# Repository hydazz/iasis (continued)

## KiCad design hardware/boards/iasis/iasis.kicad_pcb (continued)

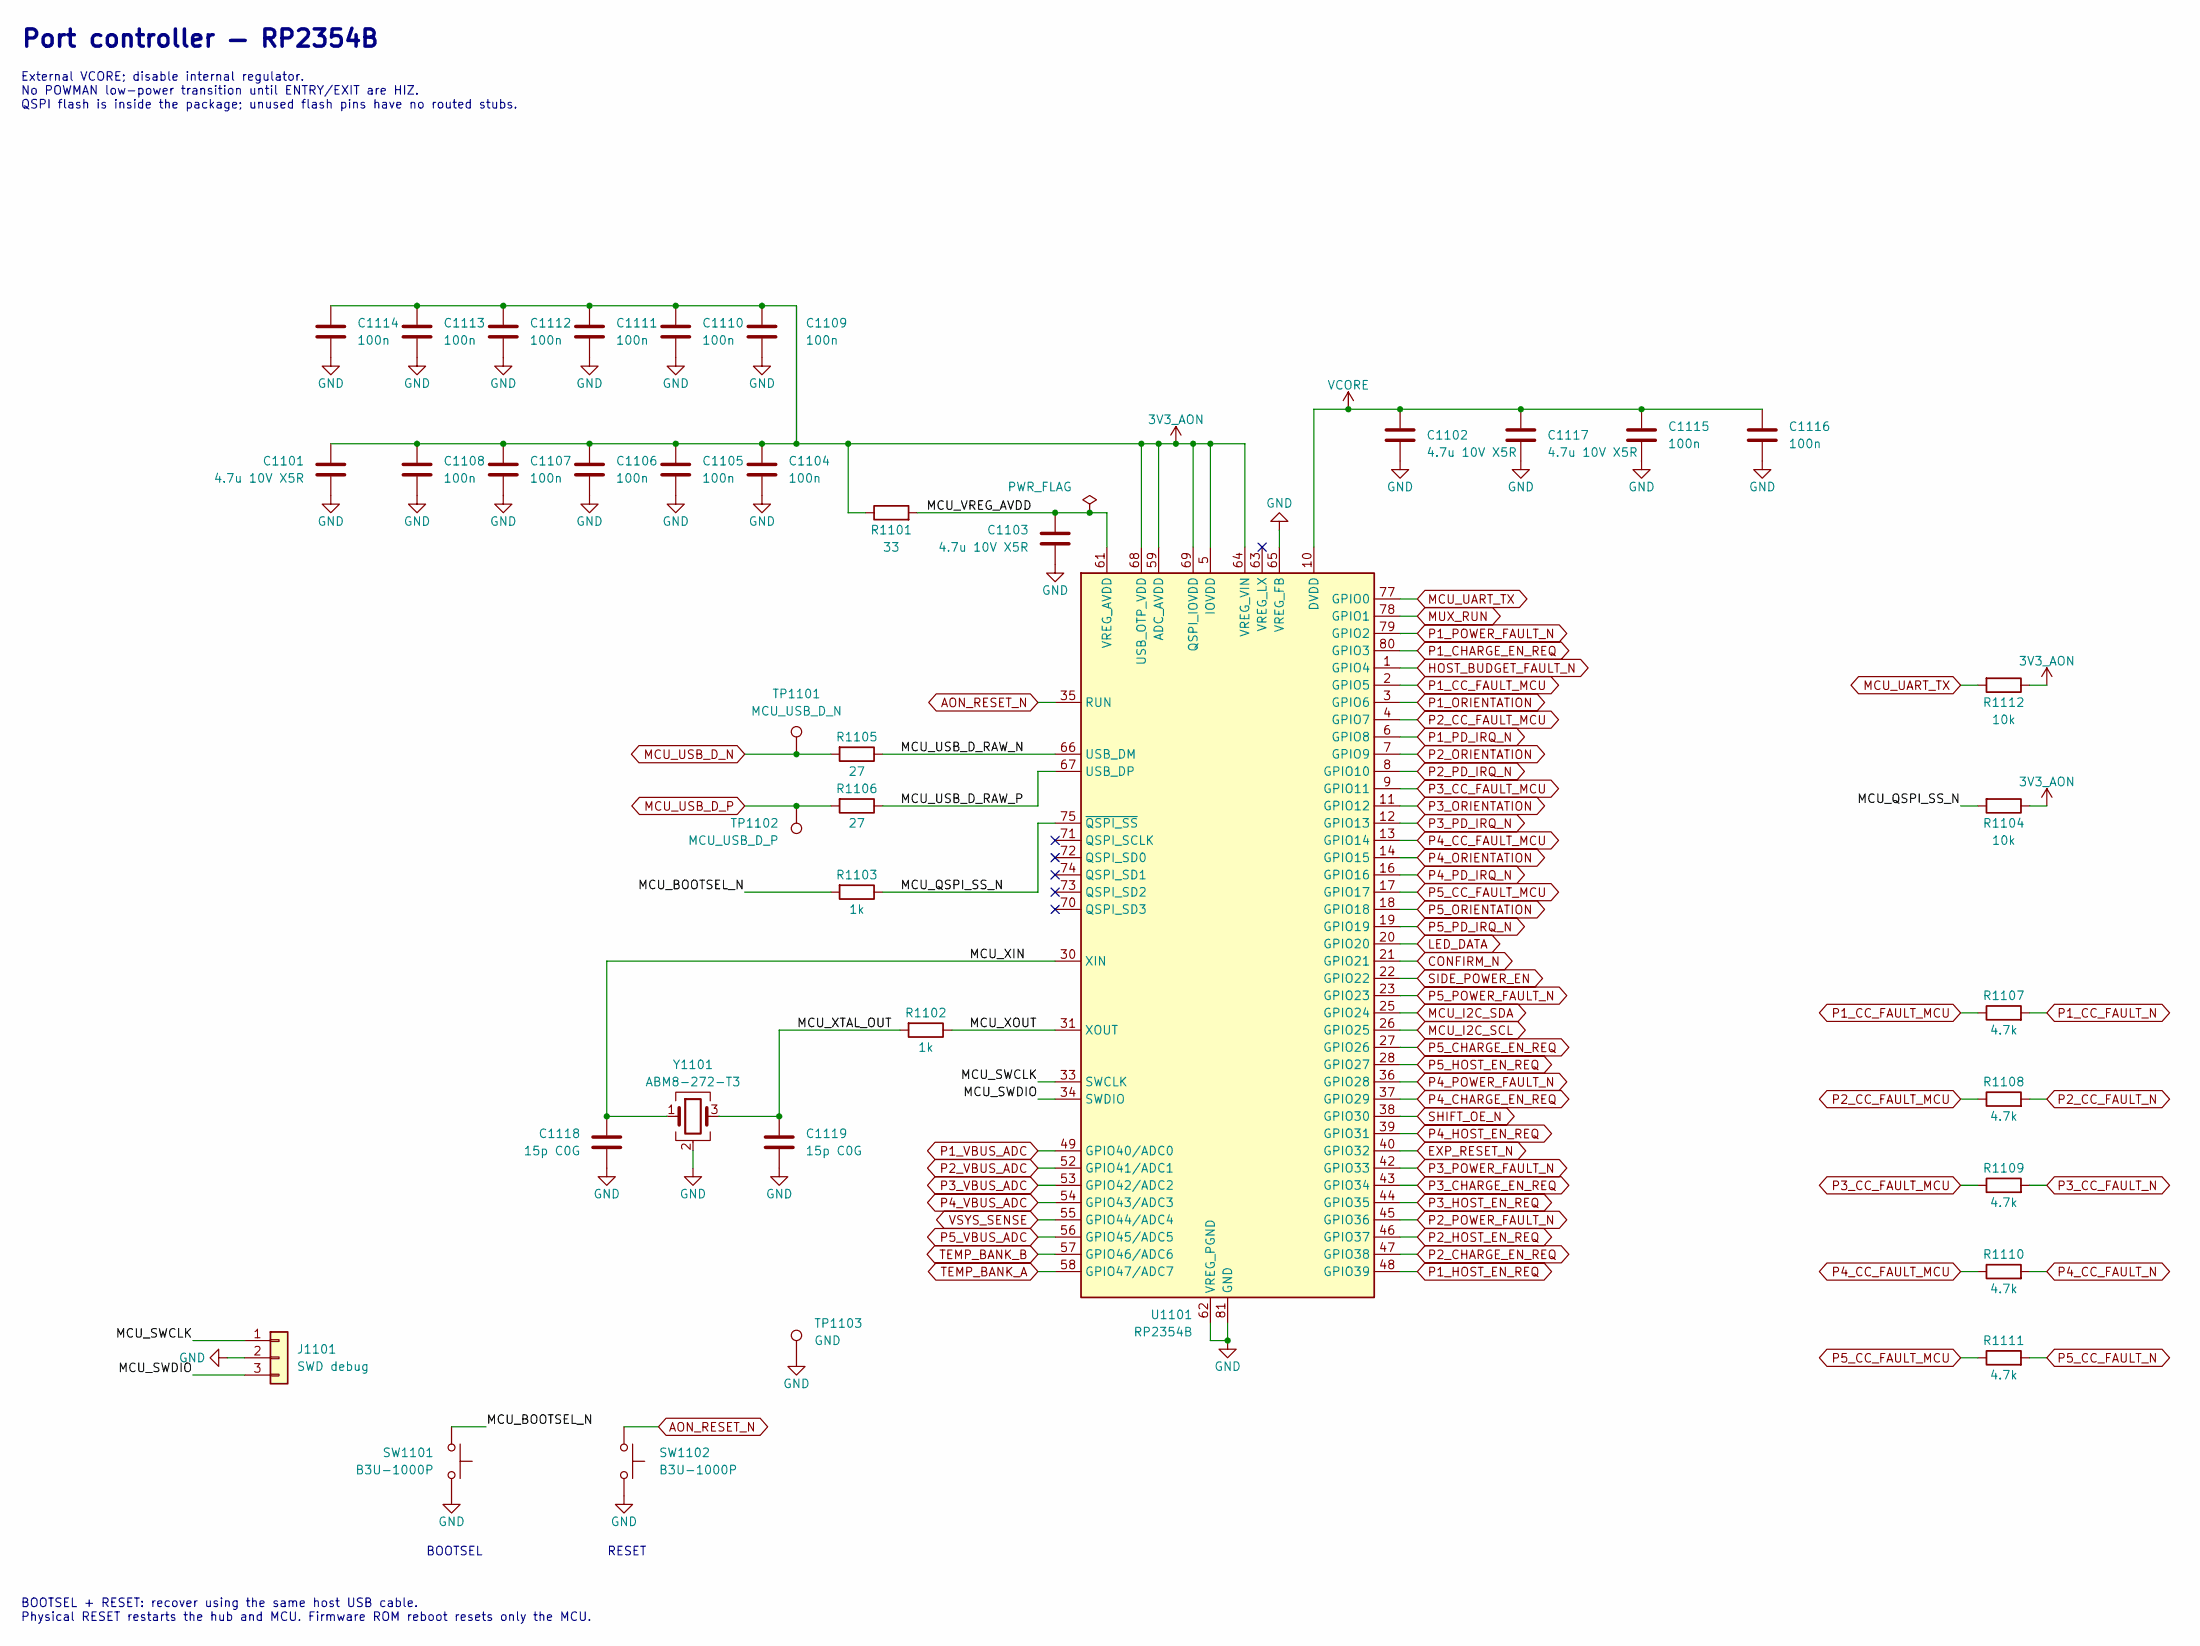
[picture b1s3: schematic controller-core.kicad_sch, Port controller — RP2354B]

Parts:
C1101, C1102: 4.7u 10V X5R; C_0402_1005Metric_WideGap; MPN CL05A475MP5NRNC; LCSC C23733
C1103, C1117: 4.7u 10V X5R; C_0402_1005Metric; MPN CL05A475MP5NRNC; LCSC C23733
C1104, C1105, C1106, C1107, C1108, C1109, C1110, C1111, C1112, C1113, C1114, C1115, C1116: 100n; C_0402_1005Metric; MPN CL05B104KO5NNNC; LCSC C1525
C1118, C1119: 15p C0G; C_0402_1005Metric; MPN 0402CG150J500NT; LCSC C1548
J1101: SWD debug; SolderPads_1x03_P2.54mm
R1101: 33; R_0402_1005Metric; MPN 0402WGF330JTCE; LCSC C25105
R1102, R1103: 1k; R_0402_1005Metric; MPN 0402WGF1001TCE; LCSC C11702
R1104, R1112: 10k; R_0402_1005Metric; MPN 0402WGF1002TCE; LCSC C25744
R1105, R1106: 27; R_0402_1005Metric; MPN RC-02K27R0FT; LCSC C140174
R1107, R1108, R1109, R1110, R1111: 4.7k; R_0402_1005Metric; MPN 0402WGF4701TCE; LCSC C25900
SW1101, SW1102: B3U-1000P; SW_SPST_B3U-1000P; MPN B3U-1000P; LCSC C231329
TP1101: MCU_USB_D_N; TestPoint_Pad_D0.5mm
TP1102: MCU_USB_D_P; TestPoint_Pad_D0.5mm
TP1103: GND; TestPoint_Pad_D1.0mm
U1101: RP2354B; QFN-80-1EP_10x10mm_P0.4mm_EP3.4x3.4mm; MPN RP2354B; LCSC C39843328
Y1101: ABM8-272-T3; Crystal_SMD_3225-4Pin_3.2x2.5mm; MPN ABM8-272-T3; LCSC C20625731

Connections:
3V3_AON: C1101.1, C1104.1, C1105.1, C1106.1, C1107.1, C1108.1, C1109.1, C1110.1, C1111.1, C1112.1, C1113.1, C1114.1, R1101.1, R1104.1, R1112.1, U1101.5 (IOVDD), U1101.15 (IOVDD), U1101.24 (IOVDD), U1101.29 (IOVDD), U1101.41 (IOVDD), U1101.50 (IOVDD), U1101.59 (ADC_AVDD), U1101.60 (IOVDD), U1101.64 (VREG_VIN), U1101.68 (USB_OTP_VDD), U1101.69 (QSPI_IOVDD), U1101.76 (IOVDD); also elsewhere on the board
/RP2354 controller/MCU_BOOTSEL_N: R1103.2, SW1101.1
/RP2354 controller/MCU_QSPI_SS_N: R1103.1, R1104.2, U1101.75 (~QSPI_SS)
/RP2354 controller/MCU_SWCLK: J1101.1, U1101.33 (SWCLK)
/RP2354 controller/MCU_SWDIO: J1101.3, U1101.34 (SWDIO)
/RP2354 controller/MCU_USB_D_RAW_N: R1105.1, U1101.66 (USB_DM)
/RP2354 controller/MCU_USB_D_RAW_P: R1106.1, U1101.67 (USB_DP)
/RP2354 controller/MCU_VREG_AVDD: C1103.1, R1101.2, U1101.61 (VREG_AVDD)
/RP2354 controller/MCU_XIN: C1118.1, U1101.30 (XIN), Y1101.1
/RP2354 controller/MCU_XOUT: R1102.1, U1101.31 (XOUT)
/RP2354 controller/MCU_XTAL_OUT: C1119.1, R1102.2, Y1101.3
AON_RESET_N: SW1102.1, U1101.35 (RUN); also elsewhere on the board
CONFIRM_N: U1101.21 (GPIO21); also elsewhere on the board
EXP_RESET_N: U1101.40 (GPIO32); also elsewhere on the board
GND: C1101.2, C1102.2, C1103.2, C1104.2, C1105.2, C1106.2, C1107.2, C1108.2, C1109.2, C1110.2, C1111.2, C1112.2, C1113.2, C1114.2, C1115.2, C1116.2, C1117.2, C1118.2, C1119.2, J1101.2, SW1101.2, SW1102.2, TP1103.1 (1_1), U1101.62 (VREG_PGND), U1101.65 (VREG_FB), U1101.81 (GND), Y1101.2 (G), Y1101.4 (G); also elsewhere on the board
HOST_BUDGET_FAULT_N: U1101.1 (GPIO4); also elsewhere on the board
LED_DATA: U1101.20 (GPIO20); also elsewhere on the board
MCU_I2C_SCL: U1101.26 (GPIO25); also elsewhere on the board
MCU_I2C_SDA: U1101.25 (GPIO24); also elsewhere on the board
MCU_UART_TX: R1112.2, U1101.77 (GPIO0); also elsewhere on the board
MCU_USB_D_N: R1105.2, TP1101.1 (1_1); also elsewhere on the board
MCU_USB_D_P: R1106.2, TP1102.1 (1_1); also elsewhere on the board
MUX_RUN: U1101.78 (GPIO1); also elsewhere on the board
P1_CC_FAULT_MCU: R1107.1, U1101.2 (GPIO5)
P1_CC_FAULT_N: R1107.2; also elsewhere on the board
P1_CHARGE_EN_REQ: U1101.80 (GPIO3); also elsewhere on the board
P1_HOST_EN_REQ: U1101.48 (GPIO39); also elsewhere on the board
P1_ORIENTATION: U1101.3 (GPIO6); also elsewhere on the board
P1_PD_IRQ_N: U1101.6 (GPIO8); also elsewhere on the board
P1_POWER_FAULT_N: U1101.79 (GPIO2); also elsewhere on the board
P1_VBUS_ADC: U1101.49 (GPIO40/ADC0); also elsewhere on the board
P2_CC_FAULT_MCU: R1108.1, U1101.4 (GPIO7)
P2_CC_FAULT_N: R1108.2; also elsewhere on the board
P2_CHARGE_EN_REQ: U1101.47 (GPIO38); also elsewhere on the board
P2_HOST_EN_REQ: U1101.46 (GPIO37); also elsewhere on the board
P2_ORIENTATION: U1101.7 (GPIO9); also elsewhere on the board
P2_PD_IRQ_N: U1101.8 (GPIO10); also elsewhere on the board
P2_POWER_FAULT_N: U1101.45 (GPIO36); also elsewhere on the board
P2_VBUS_ADC: U1101.52 (GPIO41/ADC1); also elsewhere on the board
P3_CC_FAULT_MCU: R1109.1, U1101.9 (GPIO11)
P3_CC_FAULT_N: R1109.2; also elsewhere on the board
P3_CHARGE_EN_REQ: U1101.43 (GPIO34); also elsewhere on the board
P3_HOST_EN_REQ: U1101.44 (GPIO35); also elsewhere on the board
P3_ORIENTATION: U1101.11 (GPIO12); also elsewhere on the board
P3_PD_IRQ_N: U1101.12 (GPIO13); also elsewhere on the board
P3_POWER_FAULT_N: U1101.42 (GPIO33); also elsewhere on the board
P3_VBUS_ADC: U1101.53 (GPIO42/ADC2); also elsewhere on the board
P4_CC_FAULT_MCU: R1110.1, U1101.13 (GPIO14)
P4_CC_FAULT_N: R1110.2; also elsewhere on the board
P4_CHARGE_EN_REQ: U1101.37 (GPIO29); also elsewhere on the board
P4_HOST_EN_REQ: U1101.39 (GPIO31); also elsewhere on the board
P4_ORIENTATION: U1101.14 (GPIO15); also elsewhere on the board
P4_PD_IRQ_N: U1101.16 (GPIO16); also elsewhere on the board
P4_POWER_FAULT_N: U1101.36 (GPIO28); also elsewhere on the board
P4_VBUS_ADC: U1101.54 (GPIO43/ADC3); also elsewhere on the board
P5_CC_FAULT_MCU: R1111.1, U1101.17 (GPIO17)
P5_CC_FAULT_N: R1111.2; also elsewhere on the board
P5_CHARGE_EN_REQ: U1101.27 (GPIO26); also elsewhere on the board
P5_HOST_EN_REQ: U1101.28 (GPIO27); also elsewhere on the board
P5_ORIENTATION: U1101.18 (GPIO18); also elsewhere on the board
P5_PD_IRQ_N: U1101.19 (GPIO19); also elsewhere on the board
P5_POWER_FAULT_N: U1101.23 (GPIO23); also elsewhere on the board
P5_VBUS_ADC: U1101.56 (GPIO45/ADC5); also elsewhere on the board
SHIFT_OE_N: U1101.38 (GPIO30); also elsewhere on the board
SIDE_POWER_EN: U1101.22 (GPIO22); also elsewhere on the board
TEMP_BANK_A: U1101.58 (GPIO47/ADC7); also elsewhere on the board
TEMP_BANK_B: U1101.57 (GPIO46/ADC6); also elsewhere on the board
VCORE: C1102.1, C1115.1, C1116.1, C1117.1, U1101.10 (DVDD), U1101.32 (DVDD), U1101.51 (DVDD); also elsewhere on the board
VSYS_SENSE: U1101.55 (GPIO44/ADC4); also elsewhere on the board

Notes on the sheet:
Port controller — RP2354B
External VCORE; disable internal regulator. No POWMAN low-power transition until ENTRY/EXIT are HIZ. QSPI flash is inside the package; unused flash pins have no routed stubs.
BOOTSEL + RESET: recover using the same host USB cable. Physical RESET restarts the hub and MCU. Firmware ROM reboot resets only the MCU.
RESET
BOOTSEL

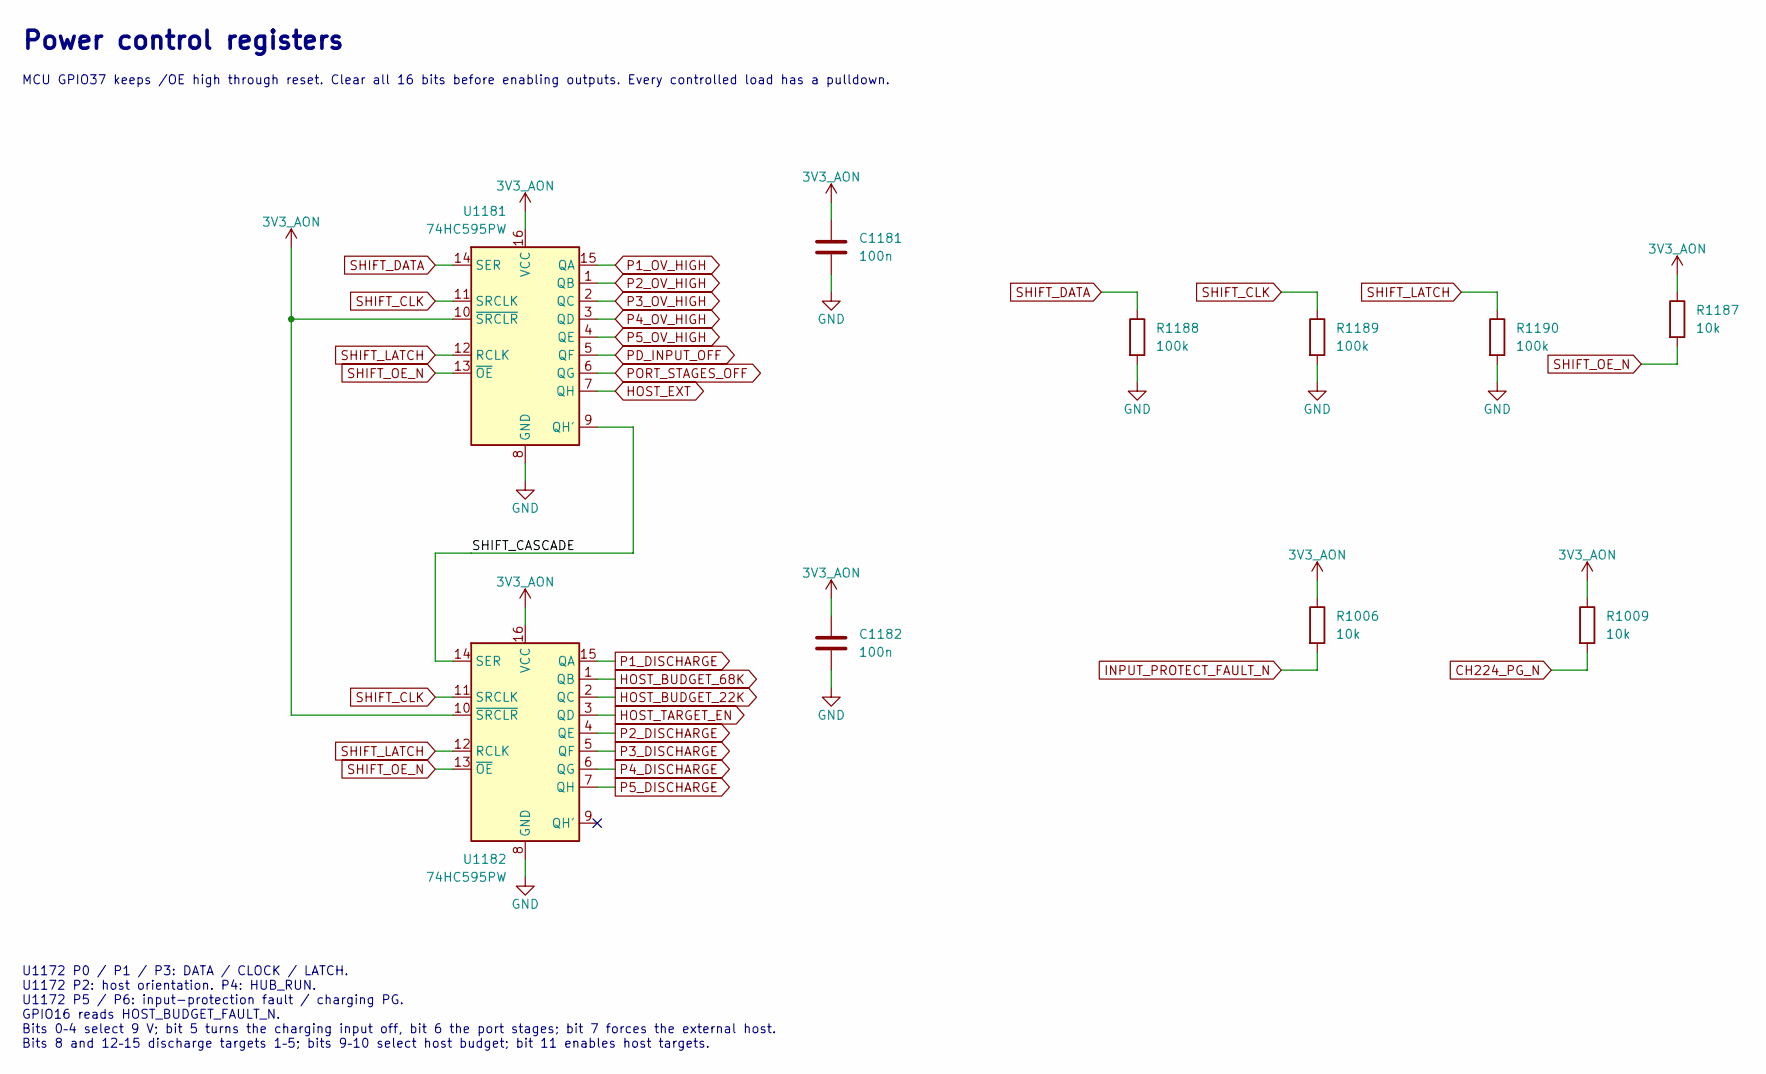
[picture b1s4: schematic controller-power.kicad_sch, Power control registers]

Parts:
C1181, C1182: 100n; C_0402_1005Metric; MPN CL05B104KO5NNNC; LCSC C1525
R1006, R1009, R1187: 10k; R_0402_1005Metric; MPN 0402WGF1002TCE; LCSC C25744
R1188, R1189, R1190: 100k; R_0402_1005Metric; MPN 0402WGF1003TCE; LCSC C25741
U1181, U1182: 74HC595PW; TSSOP-16_4.4x5mm_P0.65mm; MPN 74HC595PW,118; LCSC C5948

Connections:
3V3_AON: C1181.1, C1182.1, R1006.1, R1009.1, R1187.1, U1181.10 (~SRCLR), U1181.16 (VCC), U1182.10 (~SRCLR), U1182.16 (VCC); also elsewhere on the board
/Power control outputs/SHIFT_CASCADE: U1181.9 (QH'), U1182.14 (SER)
CH224_PG_N: R1009.2; also elsewhere on the board
GND: C1181.2, C1182.2, R1188.2, R1189.2, R1190.2, U1181.8 (GND), U1182.8 (GND); also elsewhere on the board
HOST_BUDGET_22K: U1182.2 (QC); also elsewhere on the board
HOST_BUDGET_68K: U1182.1 (QB); also elsewhere on the board
HOST_EXT: U1181.7 (QH); also elsewhere on the board
HOST_TARGET_EN: U1182.3 (QD); also elsewhere on the board
INPUT_PROTECT_FAULT_N: R1006.2; also elsewhere on the board
P1_DISCHARGE: U1182.15 (QA); also elsewhere on the board
P1_OV_HIGH: U1181.15 (QA); also elsewhere on the board
P2_DISCHARGE: U1182.4 (QE); also elsewhere on the board
P2_OV_HIGH: U1181.1 (QB); also elsewhere on the board
P3_DISCHARGE: U1182.5 (QF); also elsewhere on the board
P3_OV_HIGH: U1181.2 (QC); also elsewhere on the board
P4_DISCHARGE: U1182.6 (QG); also elsewhere on the board
P4_OV_HIGH: U1181.3 (QD); also elsewhere on the board
P5_DISCHARGE: U1182.7 (QH); also elsewhere on the board
P5_OV_HIGH: U1181.4 (QE); also elsewhere on the board
PD_INPUT_OFF: U1181.5 (QF); also elsewhere on the board
PORT_STAGES_OFF: U1181.6 (QG); also elsewhere on the board
SHIFT_CLK: R1189.1, U1181.11 (SRCLK), U1182.11 (SRCLK); also elsewhere on the board
SHIFT_DATA: R1188.1, U1181.14 (SER); also elsewhere on the board
SHIFT_LATCH: R1190.1, U1181.12 (RCLK), U1182.12 (RCLK); also elsewhere on the board
SHIFT_OE_N: R1187.2, U1181.13 (~OE), U1182.13 (~OE); also elsewhere on the board

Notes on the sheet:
U1172 P0 / P1 / P3: DATA / CLOCK / LATCH. U1172 P2: host orientation. P4: HUB_RUN. U1172 P5 / P6: input-protection fault / charging PG. GPIO16 reads HOST_BUDGET_FAULT_N. Bits 0–4 select 9 V; bit 5 turns the charging input off, bit 6 the port stages; bit 7 forces the external host. Bits 8 and 12–15 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
MCU GPIO37 keeps /OE high through reset. Clear all 16 bits before enabling outputs. Every controlled load has a pulldown.
Power control registers

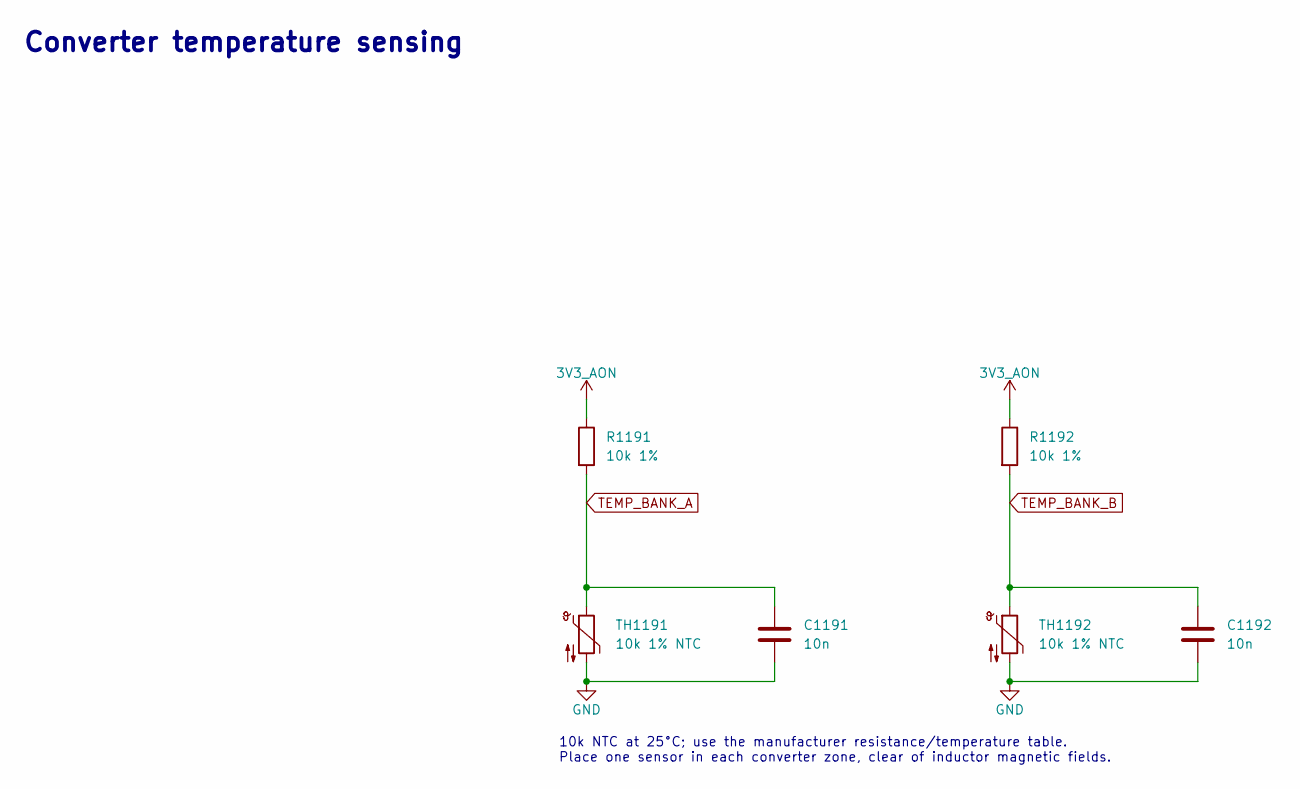
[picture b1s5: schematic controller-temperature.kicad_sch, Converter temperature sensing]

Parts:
C1191, C1192: 10n; C_0402_1005Metric; MPN CL05B103KB5NNNC; LCSC C15195
R1191, R1192: 10k 1%; R_0402_1005Metric; MPN 0402WGF1002TCE; LCSC C25744
TH1191, TH1192: 10k 1% NTC; R_0603_1608Metric; MPN NCU18XH103F60RB; LCSC C440252

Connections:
3V3_AON: R1191.1, R1192.1; also elsewhere on the board
GND: C1191.2, C1192.2, TH1191.2, TH1192.2; also elsewhere on the board
TEMP_BANK_A: C1191.1, R1191.2, TH1191.1; also elsewhere on the board
TEMP_BANK_B: C1192.1, R1192.2, TH1192.1; also elsewhere on the board

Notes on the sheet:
Converter temperature sensing
10k NTC at 25°C; use the manufacturer resistance/temperature table. Place one sensor in each converter zone, clear of inductor magnetic fields.

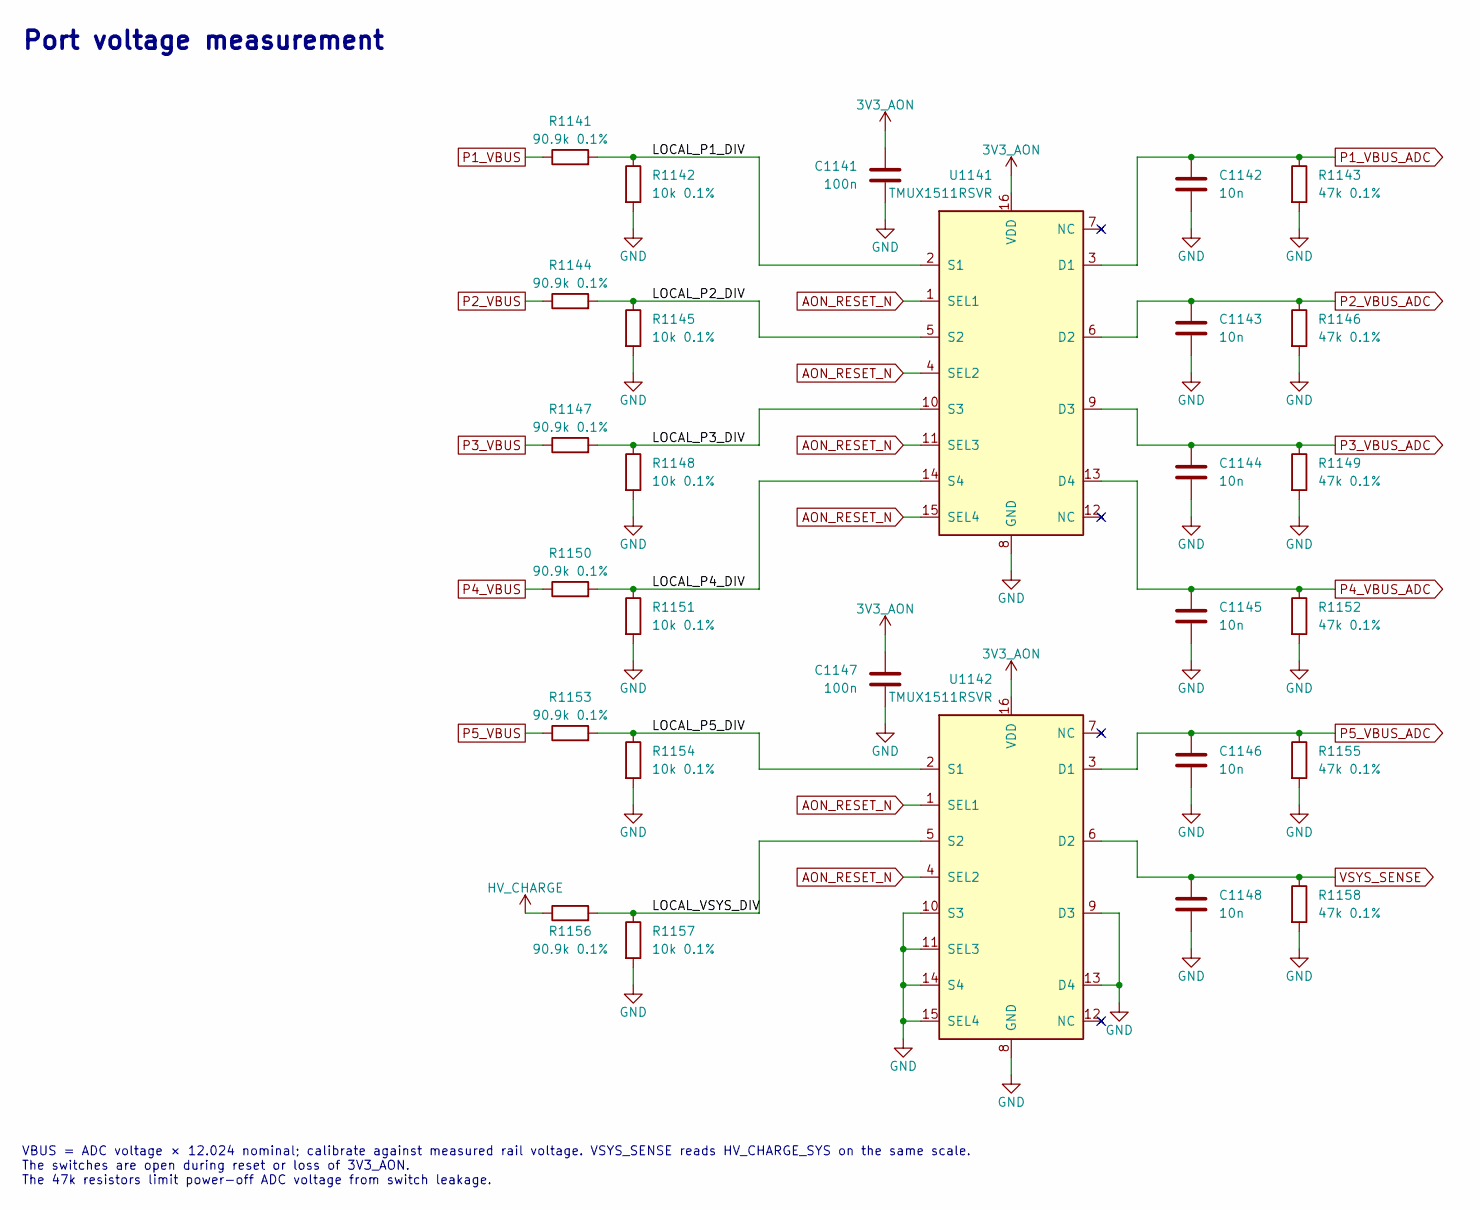
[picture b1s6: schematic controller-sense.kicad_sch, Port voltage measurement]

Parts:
C1141, C1147: 100n; C_0402_1005Metric; MPN CL05B104KO5NNNC; LCSC C1525
C1142, C1143, C1144, C1145, C1146, C1148: 10n; C_0402_1005Metric; MPN CL05B103KB5NNNC; LCSC C15195
R1141, R1144, R1147, R1150, R1153, R1156: 90.9k 0.1%; R_0402_1005Metric; MPN RT0402BRD0790K9L; LCSC C852949
R1142, R1145, R1148, R1151, R1154, R1157: 10k 0.1%; R_0402_1005Metric; MPN THC02H1002BT; LCSC C2991528
R1143, R1146, R1149, R1152, R1155, R1158: 47k 0.1%; R_0402_1005Metric; MPN ARG02BTC4702; LCSC C5122071
U1141, U1142: TMUX1511RSVR; UQFN-16_1.8x2.6mm_P0.4mm; MPN TMUX1511RSVR; LCSC C2673275

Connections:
3V3_AON: C1141.1, C1147.1, U1141.16 (VDD), U1142.16 (VDD); also elsewhere on the board
/Port voltage measurement/LOCAL_P1_DIV: R1141.2, R1142.1, U1141.2 (S1)
/Port voltage measurement/LOCAL_P2_DIV: R1144.2, R1145.1, U1141.5 (S2)
/Port voltage measurement/LOCAL_P3_DIV: R1147.2, R1148.1, U1141.10 (S3)
/Port voltage measurement/LOCAL_P4_DIV: R1150.2, R1151.1, U1141.14 (S4)
/Port voltage measurement/LOCAL_P5_DIV: R1153.2, R1154.1, U1142.2 (S1)
/Port voltage measurement/LOCAL_VSYS_DIV: R1156.2, R1157.1, U1142.5 (S2)
AON_RESET_N: U1141.1 (SEL1), U1141.4 (SEL2), U1141.11 (SEL3), U1141.15 (SEL4), U1142.1 (SEL1), U1142.4 (SEL2); also elsewhere on the board
GND: C1141.2, C1142.2, C1143.2, C1144.2, C1145.2, C1146.2, C1147.2, C1148.2, R1142.2, R1143.2, R1145.2, R1146.2, R1148.2, R1149.2, R1151.2, R1152.2, R1154.2, R1155.2, R1157.2, R1158.2, U1141.8 (GND), U1142.8 (GND), U1142.9 (D3), U1142.10 (S3), U1142.11 (SEL3), U1142.13 (D4), U1142.14 (S4), U1142.15 (SEL4); also elsewhere on the board
HV_CHARGE: R1156.1; also elsewhere on the board
P1_VBUS: R1141.1; also elsewhere on the board
P1_VBUS_ADC: C1142.1, R1143.1, U1141.3 (D1); also elsewhere on the board
P2_VBUS: R1144.1; also elsewhere on the board
P2_VBUS_ADC: C1143.1, R1146.1, U1141.6 (D2); also elsewhere on the board
P3_VBUS: R1147.1; also elsewhere on the board
P3_VBUS_ADC: C1144.1, R1149.1, U1141.9 (D3); also elsewhere on the board
P4_VBUS: R1150.1; also elsewhere on the board
P4_VBUS_ADC: C1145.1, R1152.1, U1141.13 (D4); also elsewhere on the board
P5_VBUS: R1153.1; also elsewhere on the board
P5_VBUS_ADC: C1146.1, R1155.1, U1142.3 (D1); also elsewhere on the board
VSYS_SENSE: C1148.1, R1158.1, U1142.6 (D2); also elsewhere on the board

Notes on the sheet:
Port voltage measurement
VBUS = ADC voltage × 12.024 nominal; calibrate against measured rail voltage. VSYS_SENSE reads HV_CHARGE_SYS on the same scale. The switches are open during reset or loss of 3V3_AON. The 47k resistors limit power-off ADC voltage from switch leakage.

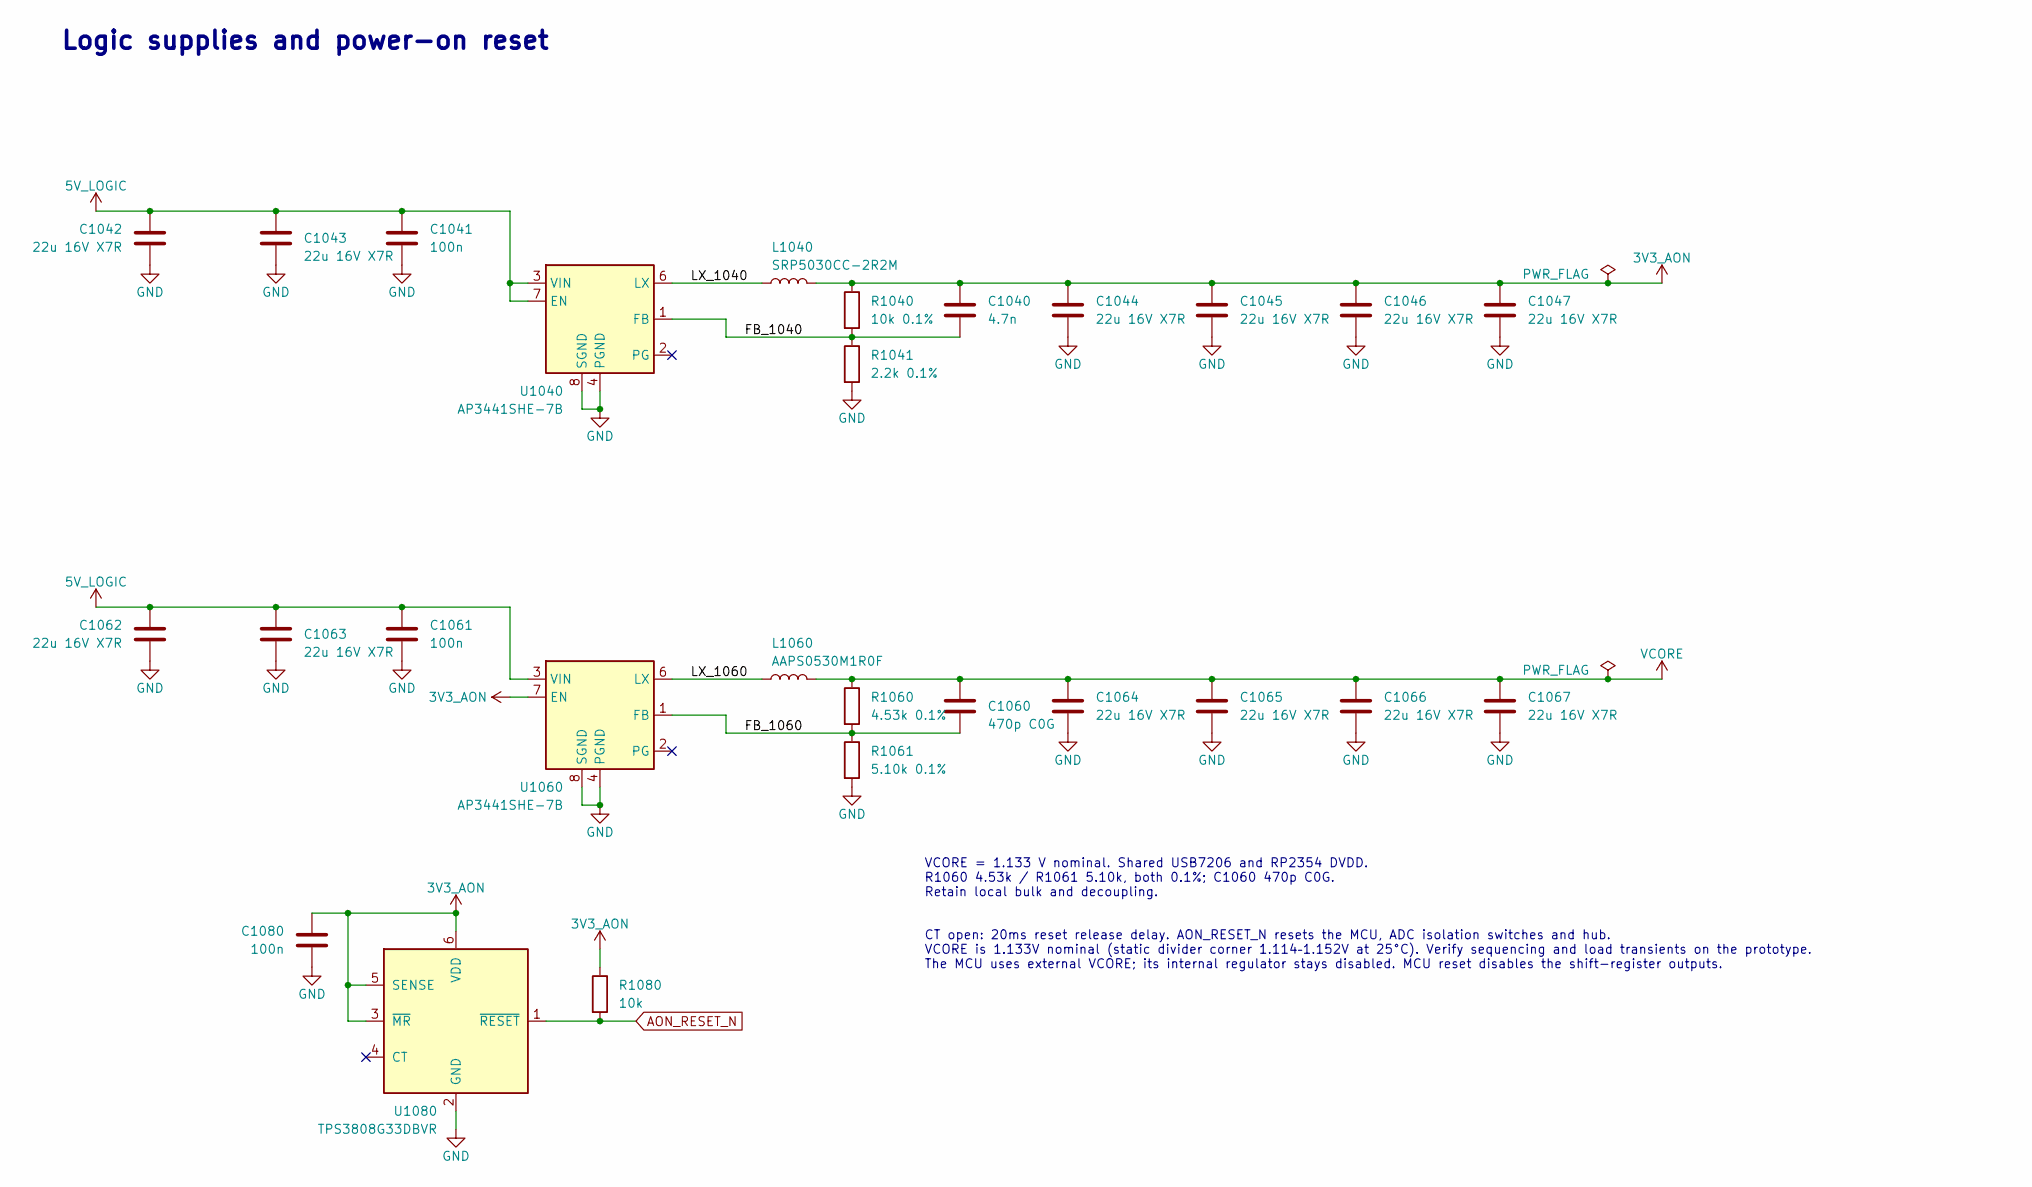
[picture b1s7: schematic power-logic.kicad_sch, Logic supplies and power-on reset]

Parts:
C1040: 4.7n; C_0402_1005Metric; MPN 0402B472K500NT; LCSC C1538
C1041, C1061, C1080: 100n; C_0402_1005Metric; MPN CL05B104KO5NNNC; LCSC C1525
C1042, C1043, C1044, C1045, C1046, C1047, C1062, C1063, C1064, C1065, C1066, C1067: 22u 16V X7R; C_1210_3225Metric; MPN CL32B226KOJNNNE; LCSC C55530
C1060: 470p C0G; C_0402_1005Metric; MPN CC0402JRNPO9BN471; LCSC C106259
L1040: SRP5030CC-2R2M; Bourns_SRP5030CC; MPN SRP5030CC-2R2M; LCSC C22404330
L1060: AAPS0530M1R0F; L_Coilcraft_XAL5030-XXX; MPN AAPS0530M1R0F; LCSC C49261451
R1040: 10k 0.1%; R_0402_1005Metric; MPN THC02H1002BT; LCSC C2991528
R1041: 2.2k 0.1%; R_0402_1005Metric; MPN RT0402BRE072K2L; LCSC C705646
R1060: 4.53k 0.1%; R_0402_1005Metric; MPN PTFR0402B4K53N9; LCSC C2692956
R1061: 5.10k 0.1%; R_0603_1608Metric; MPN RT0603BRB075K1L; LCSC C860455
R1080: 10k; R_0402_1005Metric; MPN 0402WGF1002TCE; LCSC C25744
U1040, U1060: AP3441SHE-7B; DFN-8-1EP_2x2mm_P0.5mm_EP0.9x1.7mm; MPN AP3441SHE-7B; LCSC C2070918
U1080: TPS3808G33DBVR; SOT-23-6; MPN TPS3808G33DBVR; LCSC C43698

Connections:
3V3_AON: C1040.1, C1044.1, C1045.1, C1046.1, C1047.1, C1080.1, L1040.2, R1040.1, R1080.1, U1060.7 (EN), U1080.3 (~MR), U1080.5 (SENSE), U1080.6 (VDD); also elsewhere on the board
5V_LOGIC: C1041.1, C1042.1, C1043.1, C1061.1, C1062.1, C1063.1, U1040.3 (VIN), U1040.7 (EN), U1060.3 (VIN); also elsewhere on the board
/Logic supplies and reset/FB_1040: C1040.2, R1040.2, R1041.1, U1040.1 (FB)
/Logic supplies and reset/FB_1060: C1060.2, R1060.2, R1061.1, U1060.1 (FB)
/Logic supplies and reset/LX_1040: L1040.1, U1040.6 (LX)
/Logic supplies and reset/LX_1060: L1060.1, U1060.6 (LX)
AON_RESET_N: R1080.2, U1080.1 (~RESET); also elsewhere on the board
GND: C1041.2, C1042.2, C1043.2, C1044.2, C1045.2, C1046.2, C1047.2, C1061.2, C1062.2, C1063.2, C1064.2, C1065.2, C1066.2, C1067.2, C1080.2, R1041.2, R1061.2, U1040.4 (PGND), U1040.8 (SGND), U1040.9 (SGND), U1060.4 (PGND), U1060.8 (SGND), U1060.9 (SGND), U1080.2 (GND); also elsewhere on the board
VCORE: C1060.1, C1064.1, C1065.1, C1066.1, C1067.1, L1060.2, R1060.1; also elsewhere on the board

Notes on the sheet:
Logic supplies and power-on reset
VCORE = 1.133 V nominal. Shared USB7206 and RP2354 DVDD. R1060 4.53k / R1061 5.10k, both 0.1%; C1060 470p C0G. Retain local bulk and decoupling.
CT open: 20ms reset release delay. AON_RESET_N resets the MCU, ADC isolation switches and hub. VCORE is 1.133V nominal (static divider corner 1.114–1.152V at 25°C). Verify sequencing and load transients on the prototype. The MCU uses external VCORE; its internal regulator stays disabled. MCU reset 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

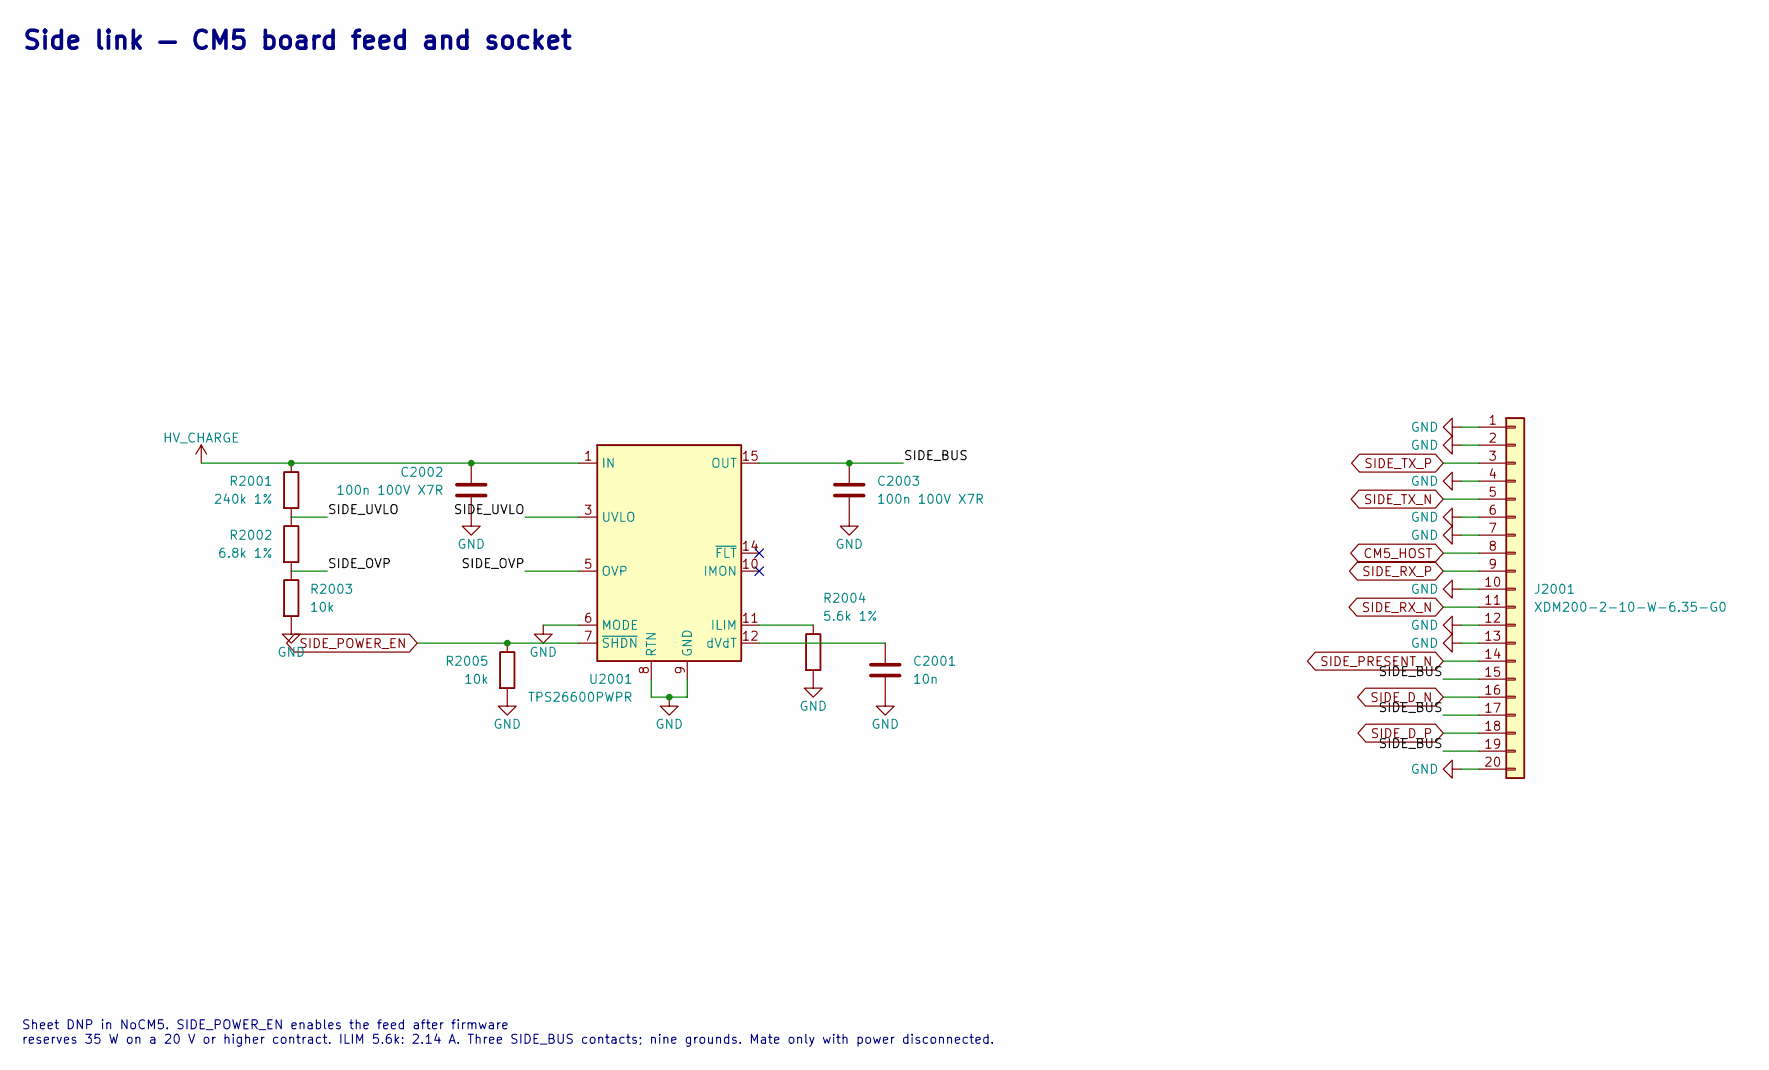
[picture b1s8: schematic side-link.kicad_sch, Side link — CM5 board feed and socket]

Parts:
C2001: 10n; C_0402_1005Metric; MPN CL05B103KB5NNNC; LCSC C15195
C2002, C2003: 100n 100V X7R; C_0603_1608Metric; MPN CC0603KRX7R0BB104; LCSC C113803
J2001: XDM200-2-10-W-6.35-G0; PinSocket_2x10_P2.00mm_Horizontal; MPN XDM200-2-10-W-6.35-G0; LCSC C19268939
R2001: 240k 1%; R_0402_1005Metric; MPN 0402WGF2403TCE; LCSC C64043
R2002: 6.8k 1%; R_0402_1005Metric; MPN 0402WGF6801TCE; LCSC C25917
R2003, R2005: 10k; R_0402_1005Metric; MPN 0402WGF1002TCE; LCSC C25744
R2004: 5.6k 1%; R_0402_1005Metric; MPN 0402WGF5601TCE; LCSC C25908
U2001: TPS26600PWPR; HTSSOP-16-1EP_4.4x5mm_P0.65mm_EP3.4x5mm_Mask2.66x2.46mm_The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; MPN TPS26600PWPR; LCSC C544399

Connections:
/Side link/SIDE_BUS: C2003.1, J2001.15, J2001.17, J2001.19, U2001.15 (OUT), U2001.16 (OUT)
/Side link/SIDE_OVP: R2002.2, R2003.1, U2001.5 (OVP)
/Side link/SIDE_UVLO: R2001.2, R2002.1, U2001.3 (UVLO)
CM5_HOST: J2001.8; also elsewhere on the board
GND: C2001.2, C2002.2, C2003.2, J2001.1, J2001.2, J2001.4, J2001.6, J2001.7, J2001.10, J2001.12, J2001.13, J2001.20, R2003.2, R2004.2, R2005.2, U2001.6 (MODE), U2001.8 (RTN), U2001.9 (GND), U2001.17 (RTN); also elsewhere on the board
HV_CHARGE: C2002.1, R2001.1, U2001.1 (IN), U2001.2 (IN); also elsewhere on the board
unnamed: R2004.1, U2001.11 (ILIM)
unnamed: C2001.1, U2001.12 (dVdT)
SIDE_D_N: J2001.16; also elsewhere on the board
SIDE_D_P: J2001.18; also elsewhere on the board
SIDE_POWER_EN: R2005.1, U2001.7 (~SHDN); also elsewhere on the board
SIDE_PRESENT_N: J2001.14; also elsewhere on the board
SIDE_RX_N: J2001.11; also elsewhere on the board
SIDE_RX_P: J2001.9; also elsewhere on the board
SIDE_TX_N: J2001.5; also elsewhere on the board
SIDE_TX_P: J2001.3; also elsewhere on the board

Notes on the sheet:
Side link — CM5 board feed and socket
Sheet DNP in NoCM5. SIDE_POWER_EN enables the feed after firmware reserves 35 W on a 20 V or higher contract. ILIM 5.6k: 2.14 A. Three SIDE_BUS contacts; nine grounds. Mate only with power disconnected.
